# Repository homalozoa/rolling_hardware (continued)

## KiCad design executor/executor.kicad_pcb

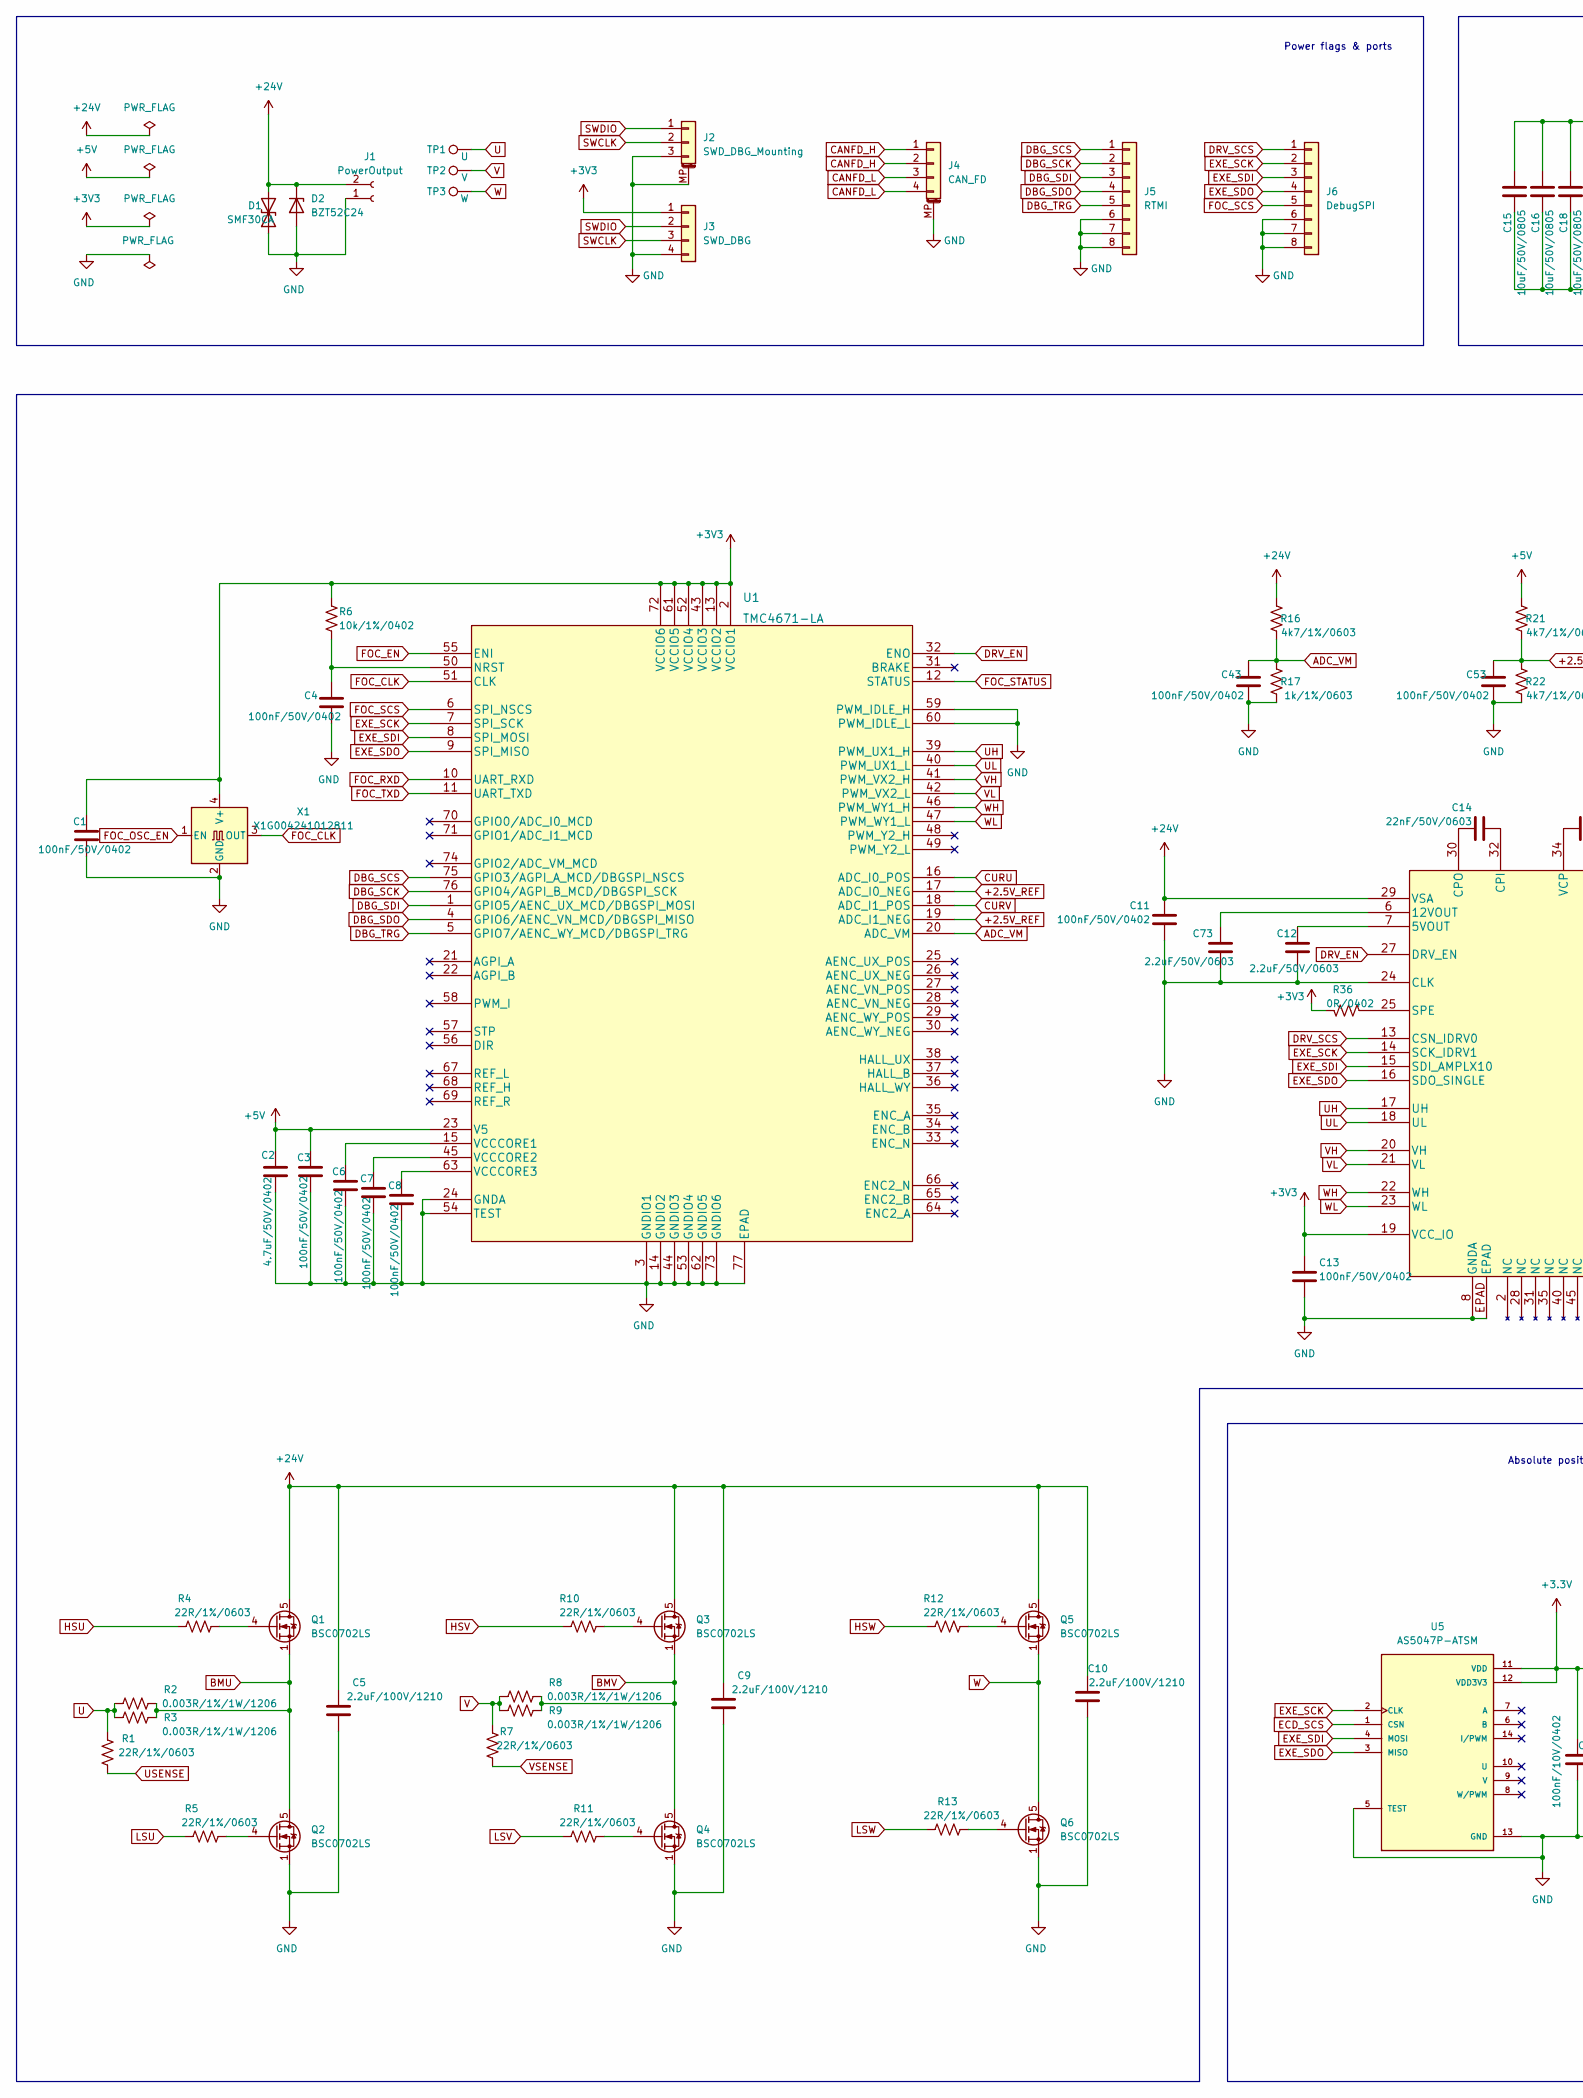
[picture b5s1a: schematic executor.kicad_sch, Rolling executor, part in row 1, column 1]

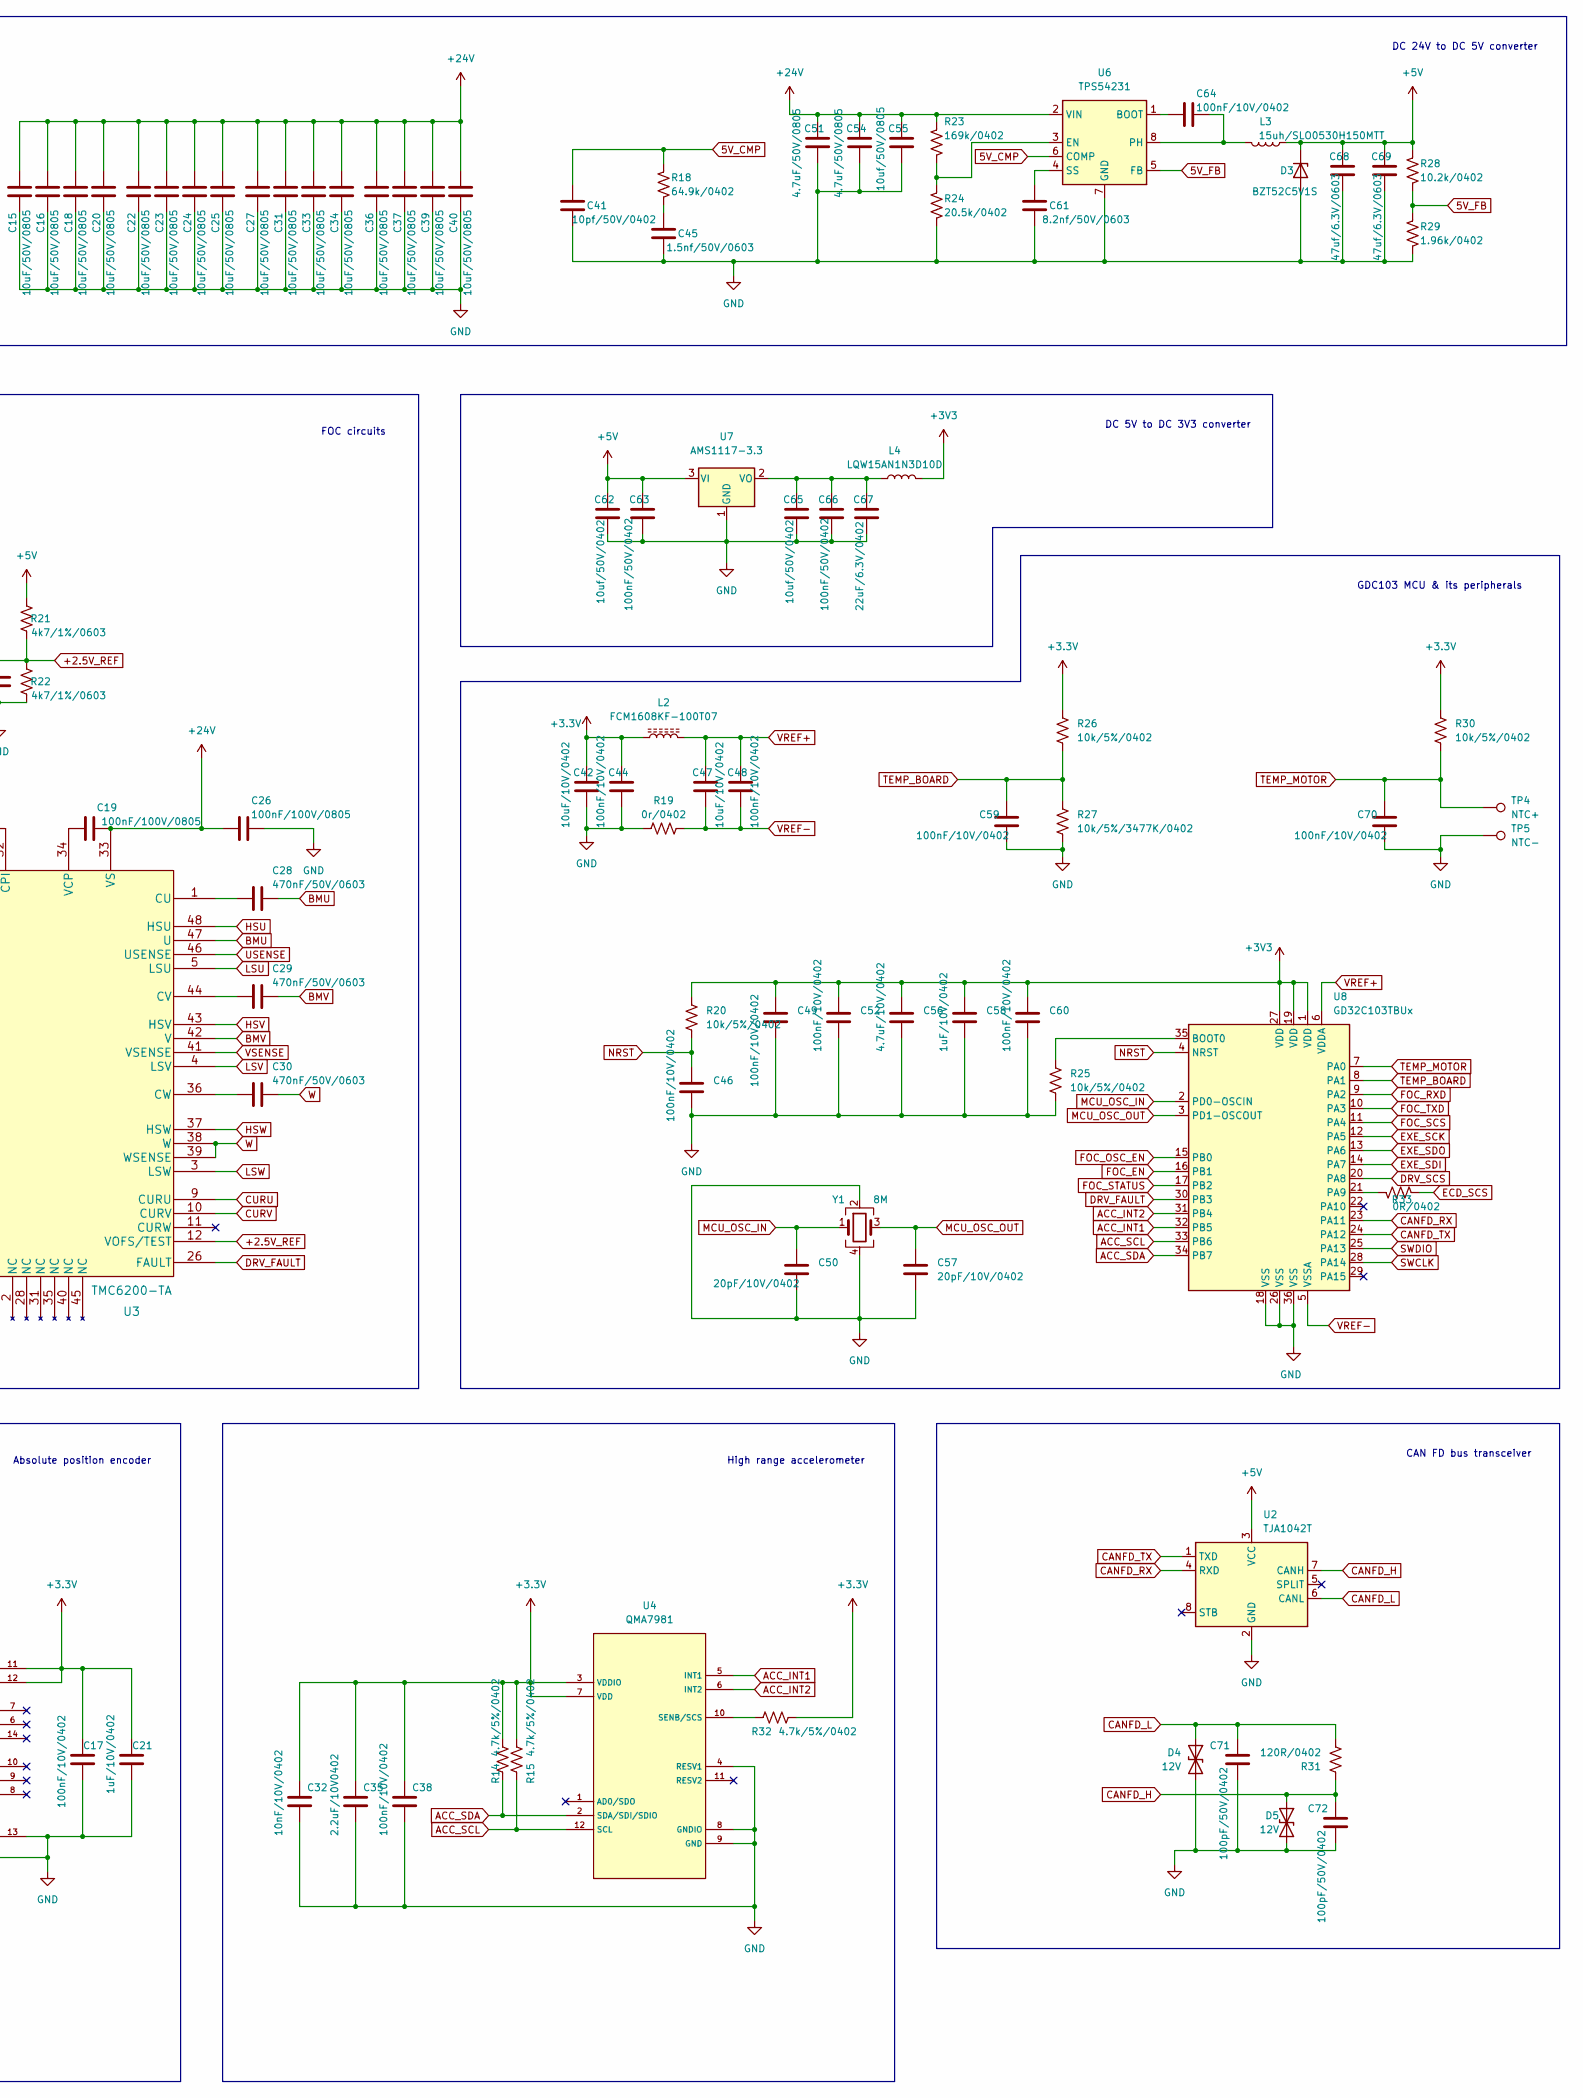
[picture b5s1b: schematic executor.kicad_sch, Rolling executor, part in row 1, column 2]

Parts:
C1, C3, C4, C6, C7, C8, C11, C13, C43, C53, C63, C66: 100nF/50V/0402; C_0402_1005Metric
C2: 4.7uF/50V/0402; C_0402_1005Metric
C5, C9, C10: 2.2uF/100V/1210; C_1210_3225Metric
C12, C73: 2.2uF/50V/0603; C_0603_1608Metric
C14: 22nF/50V/0603; C_0603_1608Metric
C15, C16, C18, C20, C22, C23, C24, C25, C27, C31, C33, C34, C36, C37, C39, C40: 10uF/50V/0805; C_0805_2012Metric
C17, C38, C44, C46, C48, C49, C52, C59, C60, C64, C70: 100nF/10V/0402; C_0402_1005Metric
C19, C26: 100nF/100V/0805; C_0805_2012Metric
C21, C58: 1uF/10V/0402; C_0402_1005Metric
C28, C29, C30: 470nF/50V/0603; C_0603_1608Metric
C32: 10nF/10V/0402; C_0402_1005Metric
C35: 2.2uF/10V0402; C_0402_1005Metric
C41: 10pf/50V/0402; C_0402_1005Metric
C42, C47: 10uF/10V/0402; C_0402_1005Metric
C45: 1.5nf/50V/0603; C_0603_1608Metric
C50, C57: 20pF/10V/0402; C_0402_1005Metric
C51, C54: 4.7uF/50V/0805; C_0805_2012Metric
C55: 10uf/50V/0805; C_0805_2012Metric
C56: 4.7uF/10V/0402; C_0402_1005Metric
C61: 8.2nf/50V/0603; C_0603_1608Metric
C62, C65: 10uf/50V/0402; C_0402_1005Metric
C67: 22uF/6.3V/0402; C_0402_1005Metric
C68, C69: 47uf/6.3V/0603; C_0603_1608Metric
C71, C72: 100pF/50V/0402; C_0402_1005Metric
D1: SMF30CA; D_SOD-123
D2: BZT52C24; D_SOD-123F
D3: BZT52C5V1S; D_SOD-123F
D4, D5: 12V; D_SOD-323
J1: PowerOutput; AMASS_XT30UPB-M_1x02_P5.0mm_Vertical
J2: SWD_DBG_Mounting; JST_GH_SM03B-GHS-TB_1x03-1MP_P1.25mm_Horizontal
J3: SWD_DBG; PinHeader_1x04_P1.27mm_Vertical
J4: CAN_FD; JST_GH_SM04B-GHS-TB_1x04-1MP_P1.25mm_Horizontal
J5: RTMI; FH34SRJ-6S-0.5SH50
J6: DebugSPI; FH34SRJ-6S-0.5SH50
L2: FCM1608KF-100T07; R_0603_1608Metric
L3: 15uh/SLO0530H150MTT; L_Sunlord_MWSA0518_5.4x5.2mm
L4: LQW15AN1N3D10D; L_0402_1005Metric
Q1, Q2, Q3, Q4, Q5, Q6: BSC0702LS; TDSON-8-1
R1, R4, R5, R7, R10, R11, R12, R13: 22R/1%/0603; R_0603_1608Metric
R2, R3, R8, R9: 0.003R/1%/1W/1206; R_1206_3216Metric
R6: 10k/1%/0402; R_0402_1005Metric
R14, R15, R32: 4.7k/5%/0402; R_0402_1005Metric
R16, R21, R22: 4k7/1%/0603; R_0603_1608Metric
R17: 1k/1%/0603; R_0603_1608Metric
R18: 64.9k/0402; R_0402_1005Metric
R19: 0r/0402; R_0402_1005Metric
R20, R25, R26, R30: 10k/5%/0402; R_0402_1005Metric
R23: 169k/0402; R_0402_1005Metric
R24: 20.5k/0402; R_0402_1005Metric
R27: 10k/5%/3477K/0402; R_0402_1005Metric
R28: 10.2k/0402; R_0402_1005Metric
R29: 1.96k/0402; R_0402_1005Metric
R31: 120R/0402; R_0402_1005Metric
R33, R36: 0R/0402; R_0402_1005Metric
TP1: U; TestPoint_Plated_Hole_D2.0mm
TP2: V; TestPoint_Plated_Hole_D2.0mm
TP3: W; TestPoint_Plated_Hole_D2.0mm
TP4: NTC+; TestPoint_THTPad_D1.0mm_Drill0.5mm
TP5: NTC-; TestPoint_THTPad_D1.0mm_Drill0.5mm
U1: TMC4671-LA; QFN76_10P5X6P5_TRI
U2: TJA1042T; SOIC-8_3.9x4.9mm_P1.27mm
U3: TMC6200-TA; eTQFP48_9x9_TRI
U4: QMA7981; LGA-12_2x2mm_P0.5mm
U5: AS5047P-ATSM; TSSOP-14_4.4x5mm_P0.65mm; PARTREV 1-01
U6: TPS54231; SOIC-8_3.9x4.9mm_P1.27mm
U7: AMS1117-3.3; SOT-223-3_TabPin2
U8: GD32C103TBUx; QFN-36-1EP_6x6mm_P0.5mm
X1: X1G004241012811; Crystal_SMD_3225-4Pin_3.2x2.5mm
Y1: 8M; Oscillator_SMD_ECS_2520MV-xxx-xx-4Pin_2.5x2.0mm

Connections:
5V_CMP: C41.1, R18.1, U6.6 (COMP)
5V_FB: R28.2, R29.1, U6.5 (FB)
+2.5V_REF: C53.2, R21.2, R22.1, U1.17 (ADC_I0_NEG), U1.19 (ADC_I1_NEG), U3.12 (VOFS/TEST)
+5V: C2.1, C3.2, C62.1, C63.1, C68.1, C69.1, D3.1 (K), L3.1, R21.1, R28.1, U1.23 (V5), U2.3 (VCC), U7.3 (VI)
+24V: C5.2, C9.2, C10.2, C11.2, C15.1, C16.1, C18.1, C19.1, C20.1, C22.1, C23.1, C24.1, C25.1, C26.1, C27.1, C31.1, C33.1, C34.1, C36.1, C37.1, C39.1, C40.1, C51.1, C54.1, C55.1, D1.2 (A2), D2.1 (K), J1.2, Q1.5 (D), Q3.5 (D), Q5.5 (D), R16.1, R23.1, U3.29 (VSA), U3.33 (VS), U6.2 (VIN)
ACC_INT1: U4.5 (INT1), U8.32 (PB5)
ACC_INT2: U4.6 (INT2), U8.31 (PB4)
ACC_SCL: R15.1, U4.12 (SCL), U8.33 (PB6)
ACC_SDA: R14.1, U4.2 (SDA/SDI/SDIO), U8.34 (PB7)
ADC_VM: C43.2, R16.2, R17.1, U1.20 (ADC_VM)
BMU: C28.2, Q1.1 (S), Q1.2 (S), Q1.3 (S), Q2.5 (D), R2.2, R3.2, U3.47 (U)
BMV: C29.2, Q3.1 (S), Q3.2 (S), Q3.3 (S), Q4.5 (D), R8.2, R9.2, U3.42 (V)
CANFD_H: C72.2, D5.1 (A1), J4.1, J4.2, R31.1, U2.7 (CANH)
CANFD_L: C71.2, D4.1 (A1), J4.3, J4.4, R31.2, U2.6 (CANL)
CANFD_RX: U2.4 (RXD), U8.23 (PA11)
CANFD_TX: U2.1 (TXD), U8.24 (PA12)
CURU: U1.16 (ADC_I0_POS), U3.9 (CURU)
CURV: U1.18 (ADC_I1_POS), U3.10 (CURV)
DBG_SCK: J5.2, U1.76 (GPIO4/AGPI_B_MCD/DBGSPI_SCK)
DBG_SCS: J5.1, U1.75 (GPIO3/AGPI_A_MCD/DBGSPI_NSCS)
DBG_SDI: J5.3, U1.1 (GPIO5/AENC_UX_MCD/DBGSPI_MOSI)
DBG_SDO: J5.4, U1.4 (GPIO6/AENC_VN_MCD/DBGSPI_MISO)
DBG_TRG: J5.5, U1.5 (GPIO7/AENC_WY_MCD/DBGSPI_TRG)
DRV_EN: U1.32 (ENO), U3.27 (DRV_EN)
DRV_FAULT: U3.26 (FAULT), U8.30 (PB3)
DRV_SCS: J6.1, U3.13 (CSN_IDRV0), U8.20 (PA8)
ECD_SCS: R33.1, U5.1 (CSN)
EXE_SCK: J6.2, U1.7 (SPI_SCK), U3.14 (SCK_IDRV1), U5.2 (CLK), U8.12 (PA5)
EXE_SDI: J6.3, U1.8 (SPI_MOSI), U3.15 (SDI_AMPLX10), U5.4 (MOSI), U8.14 (PA7)
EXE_SDO: J6.4, U1.9 (SPI_MISO), U3.16 (SDO_SINGLE), U5.3 (MISO), U8.13 (PA6)
FOC_CLK: U1.51 (CLK), X1.3 (OUT)
FOC_EN: U1.55 (ENI), U8.16 (PB1)
FOC_OSC_EN: U8.15 (PB0), X1.1 (EN)
FOC_RXD: U1.10 (UART_RXD), U8.9 (PA2)
FOC_SCS: J6.5, U1.6 (SPI_NSCS), U8.11 (PA4)
FOC_STATUS: U1.12 (STATUS), U8.17 (PB2)
FOC_TXD: U1.11 (UART_TXD), U8.10 (PA3)
GND: C1.1, C2.2, C3.1, C4.1, C5.1, C6.1, C7.1, C8.1, C9.1, C10.1, C11.1, C12.1, C13.1, C15.2, C16.2, C17.2, C18.2, C20.2, C21.2, C22.2, C23.2, C24.2, C25.2, C26.2, C27.2, C31.2, C32.2, C33.2, C34.2, C35.2, C36.2, C37.2, C38.2, C39.2, C40.2, C41.2, C42.1, C43.1, C44.1, C45.2, C46.2, C49.2, C50.1, C51.2, C52.2, C53.1, C54.2, C55.2, C56.2, C57.1, C58.2, C59.1, C60.2, C61.2, C62.2, C63.2, C65.2, C66.2, C67.2, C68.2, C69.2, C70.1, C71.1, C72.1, C73.1, D1.1 (A1), D2.2 (A), D3.2 (A), D4.2 (A2), D5.2 (A2), J1.1, J2.3, J2.MP (MountPin), J3.4, J4.MP (MountPin), J5.6, J5.7, J5.8, J6.6, J6.7, J6.8, Q2.1 (S), Q2.2 (S), Q2.3 (S), Q4.1 (S), Q4.2 (S), Q4.3 (S), Q6.1 (S), Q6.2 (S), Q6.3 (S), R17.2, R19.1, R22.2, R24.2, R25.2, R27.2, R29.2, TP5.1, U1.3 (GNDIO1), U1.14 (GNDIO2), U1.24 (GNDA), U1.44 (GNDIO3), U1.53 (GNDIO4), U1.54 (TEST), U1.59 (PWM_IDLE_H), U1.60 (PWM_IDLE_L), U1.62 (GNDIO5), U1.73 (GNDIO6), U1.77 (EPAD), U2.2 (GND), U3.8 (GNDA), U3.24 (CLK), U3.EPAD, U4.4 (RESV1), U4.8 (GNDIO), U4.9 (GND), U5.5 (TEST), U5.13 (GND), U6.7 (GND), U7.1 (GND), U8.18 (VSS), U8.26 (VSS), U8.36 (VSS), X1.2 (GND), Y1.2, Y1.4
HSU: R4.1, U3.48 (HSU)
HSV: R10.1, U3.43 (HSV)
HSW: R12.1, U3.37 (HSW)
LSU: R5.1, U3.5 (LSU)
LSV: R11.1, U3.4 (LSV)
LSW: R13.1, U3.3 (LSW)
MCU_OSC_IN: C50.2, U8.2 (PD0-OSCIN), Y1.1
MCU_OSC_OUT: C57.2, U8.3 (PD1-OSCOUT), Y1.3
NRST: C46.1, R20.2, U8.4 (NRST)
unnamed: C4.2, R6.2, U1.50 (NRST)
unnamed: C6.2, U1.15 (VCCCORE1)
unnamed: C7.2, U1.45 (VCCCORE2)
unnamed: C8.2, U1.63 (VCCCORE3)
unnamed: C12.2, U3.7 (5VOUT)
unnamed: C14.1, U3.32 (CPI)
unnamed: C14.2, U3.30 (CPO)
unnamed: C19.2, U3.34 (VCP)
unnamed: C28.1, U3.1 (CU)
unnamed: C29.1, U3.44 (CV)
unnamed: C30.1, U3.36 (CW)
unnamed: C45.1, R18.2
unnamed: C61.1, U6.4 (SS)
unnamed: C64.1, L3.2, U6.8 (PH)
unnamed: C64.2, U6.1 (BOOT)
unnamed: C65.1, C66.1, C67.1, L4.1, U7.2 (VO)
unnamed: C73.2, U3.6 (12VOUT)
unnamed: Q1.4 (G), R4.2
unnamed: Q2.4 (G), R5.2
unnamed: Q3.4 (G), R10.2
unnamed: Q4.4 (G), R11.2
unnamed: Q5.4 (G), R12.2
unnamed: Q6.4 (G), R13.2
unnamed: R23.2, R24.1, U6.3 (EN)
unnamed: R25.1, U8.35 (BOOT0)
unnamed: R32.1, U4.10 (SENB/SCS)
unnamed: R36.1, U3.25 (SPE)
unnamed: R33.2, U8.21 (PA9)
SWCLK: J2.2, J3.3, U8.28 (PA14)
SWDIO: J2.1, J3.2, U8.25 (PA13)
TEMP_BOARD: C59.2, R26.2, R27.1, U8.8 (PA1)
TEMP_MOTOR: C70.2, R30.2, TP4.1, U8.7 (PA0)
U: R1.2, R2.1, R3.1, TP1.1
UH: U1.39 (PWM_UX1_H), U3.17 (UH)
UL: U1.40 (PWM_UX1_L), U3.18 (UL)
USENSE: R1.1, U3.46 (USENSE)
V: R7.2, R8.1, R9.1, TP2.1
VH: U1.41 (PWM_VX2_H), U3.20 (VH)
VL: U1.42 (PWM_VX2_L), U3.21 (VL)
VREF+: C47.2, C48.2, L2.2, U8.6 (VDDA)
VREF-: C47.1, C48.1, R19.2, U8.5 (VSSA)
VSENSE: R7.1, U3.41 (VSENSE)
W: C30.2, Q5.1 (S), Q5.2 (S), Q5.3 (S), Q6.5 (D), TP3.1, U3.38 (W), U3.39 (WSENSE)
WH: U1.46 (PWM_WY1_H), U3.22 (WH)
WL: U1.47 (PWM_WY1_L), U3.23 (WL)

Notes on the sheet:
Absolute position encoder
High range accelerometer
FOC circuits
CAN FD bus transceiver
Power flags & ports
GDC103 MCU & its peripherals
DC 24V to DC 5V converter
DC 5V to DC 3V3 converter

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
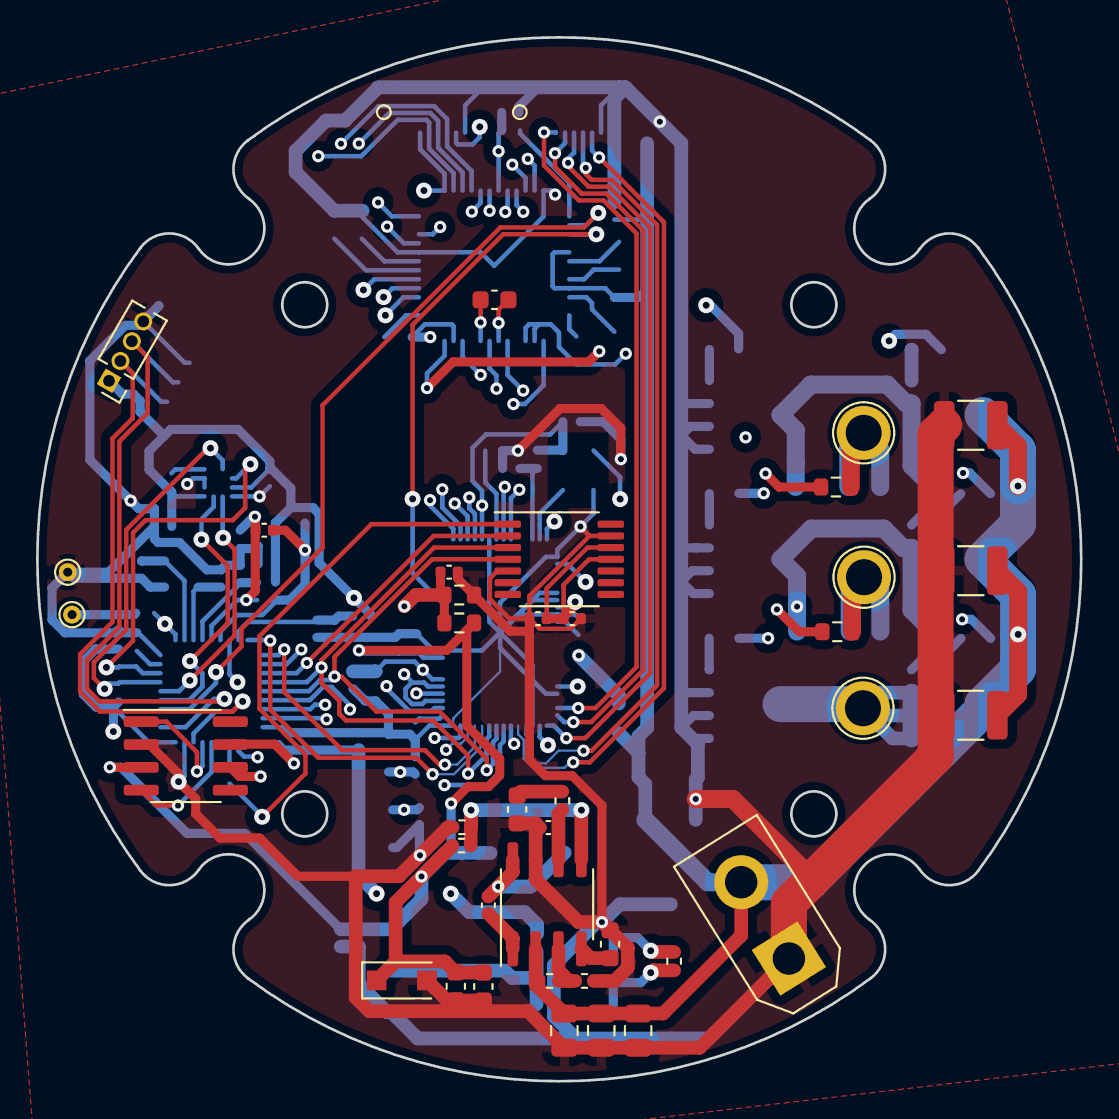
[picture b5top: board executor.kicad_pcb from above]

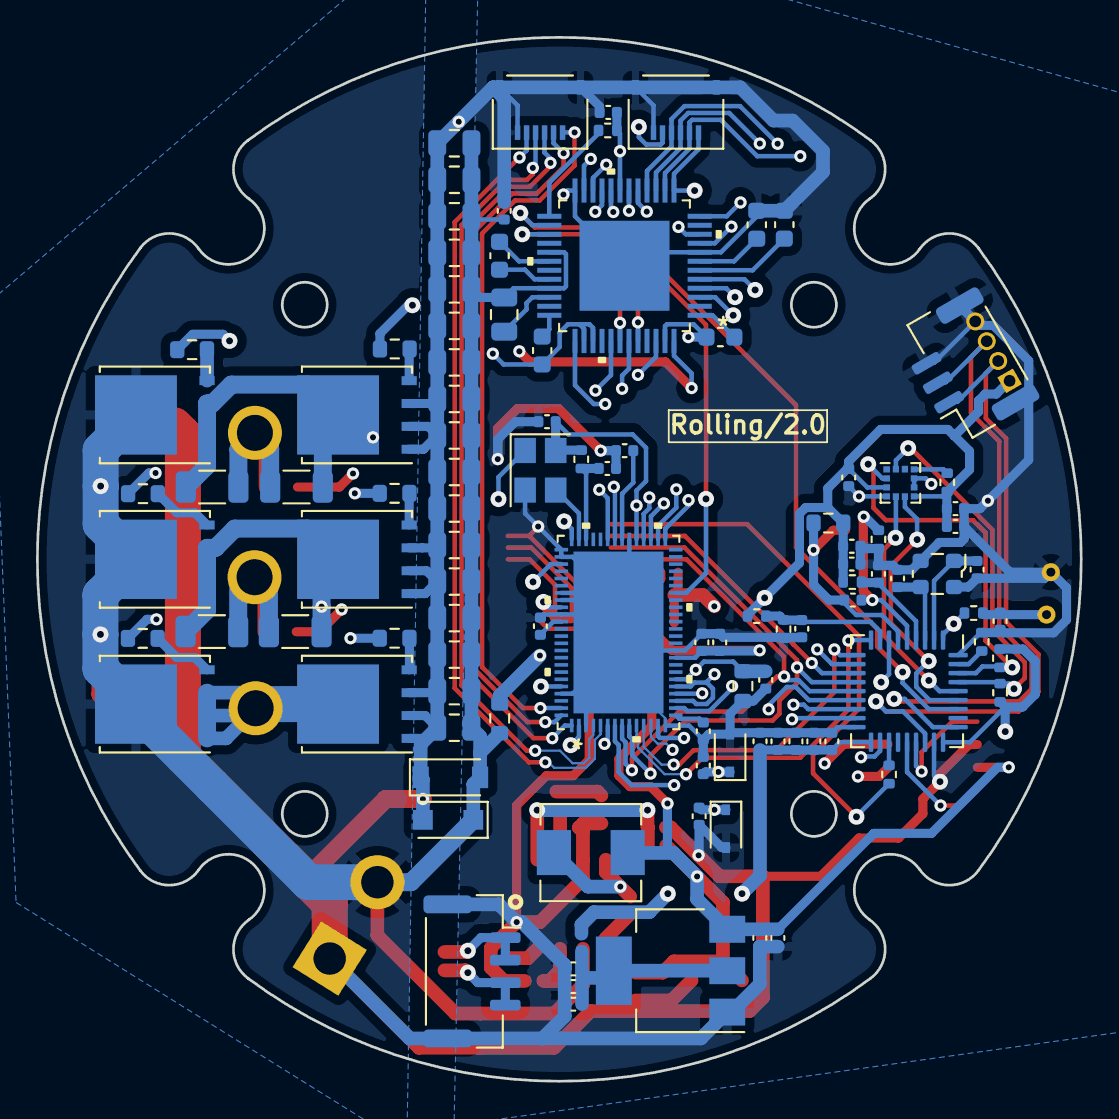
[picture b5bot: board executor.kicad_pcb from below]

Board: 4 copper layers, 58.0 x 58.0 mm, 142 parts (104 on the bottom side), 93 nets.

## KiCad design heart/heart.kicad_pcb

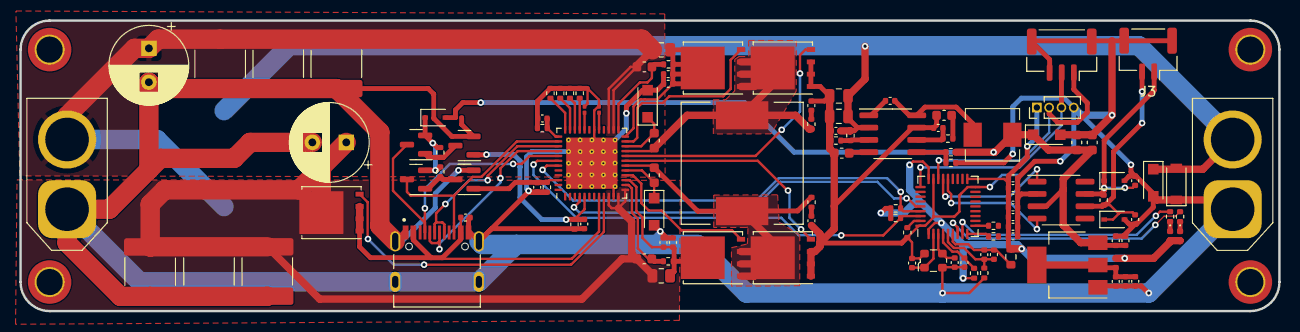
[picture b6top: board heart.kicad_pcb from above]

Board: 2 copper layers, 130.0 x 30.0 mm, 123 parts (1 on the bottom side), 67 nets.

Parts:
C1: 10pf 50V; C_0402_1005Metric
C2, C8, C14, C30: 10uf 50V; C_0402_1005Metric
C3: 1.5nf 50V; C_0603_1608Metric
C4, C11, C28, C36, C37, C39, C40, C42, C50: 100nF, 10%, 50V; C_0402_1005Metric
C5, C6: 100nF, 10%, 100V; C_0603_1608Metric
C7, C10: 4.7uF 50V; C_0805_2012Metric
C13: 22uF, 10%, 6.3V; C_0402_1005Metric
C15: 8.2nf 50V; C_0603_1608Metric
C16, C17: 100pF, 10%, 10V; C_0402_1005Metric
C18, C20, C22, C24, C29, C41, C46: 100nF, 10%, 10V; C_0402_1005Metric
C19, C21: 47uf 50V; C_0603_1608Metric
C23, C26: 20pF, 10%, 10V; C_0402_1005Metric
C25: 4.7uF, 10%, 10V; C_0402_1005Metric
C27: 1uF, 10%, 10V; C_0402_1005Metric
C31, C33: 1uf 50V; C_0603_1608Metric
C32, C34, C35: 2.2uf 50v; C_0201_0603Metric
C38, C44: 10uF, 10%, 10V; C_0402_1005Metric
C43, C49: 220uf; CP_Radial_D8.0mm_P3.50mm
C45, C47, C48, C51, C54, C55: 22uF,50V; C_2220_5650Metric
C52, C53: 1.5nF 50v; C_0402_1005Metric
D1: SMF30CA; D_SOD-123
D2: BZT52C24; D_SOD-123F
D3, D4: 12V; D_SOD-323
D5: BZT52C5V1S; D_SOD-123F
D6, D7: SMF30A; D_SOD-123F
D8: 1SS355; D_SOD-323
D9: 16-213/SDRC/S530-A3/TR8; D_0402_1005Metric
D10: 16-213/GHC-YR1S1/3T; D_0402_1005Metric
J1: BatteryPort; AMASS_XT60-M_1x02_P7.20mm_Vertical
J2: PowerOutput; AMASS_XT60-F_1x02_P7.20mm_Vertical
J3: CAN FD; JST_GH_SM02B-GHS-TB_1x02-1MP_P1.25mm_Horizontal
J4: SWD_DBG; PinHeader_1x04_P1.27mm_Vertical
J5: SWD_DBG_Mounting; JST_GH_SM03B-GHS-TB_1x03-1MP_P1.25mm_Horizontal
J8: TYPE-C-31-M-12; HRO_TYPE-C-31-M-12
L1: LQW15AN1N3D10D; L_0402_1005Metric
L2: 15uh, SLO0530H150MTT; L_Sunlord_MWSA0518_5.4x5.2mm
L3, L5: MWSA1206S-5R6MT; L_12x12mm_H6mm
L4: FCM1608KF-100T07; R_0603_1608Metric
Mount1, Mount1#2, Mount1#3, Mount1#4: MountingHole_2.7mm_M2.5_ISO7380_Pad_TopBottom
Q1: BSC0702LS; TDSON-8-1
Q2, Q6: 2301; SOT-23
Q3, Q7: 2N7002; SOT-23
Q4, Q5, Q8, Q9: NTMFS5C670NLT1G; TDSON-8-1
R1: 64.9k; R_0402_1005Metric
R2: 169k; R_0402_1005Metric
R3: 20.5; R_0402_1005Metric
R4: 120R; R_0402_1005Metric
R5, R8: 10k, 5%; R_0402_1005Metric
R6: 10.2k; R_0402_1005Metric
R7: 1.96k; R_0402_1005Metric
R9: 10k, 3380k; R_0402_1005Metric
R10, R11: 4.7k; R_0402_1005Metric
R12, R15: 27k; R_0402_1005Metric
R13: 6.2k; R_0402_1005Metric
R14, R22, R25: 10k; R_0402_1005Metric
R16, R17, R24: 0; R_0402_1005Metric
R18, R20: 10r; R_0402_1005Metric
R19, R21: 0.005r; R_0805_2012Metric
R23, R28: 1M; R_0402_1005Metric
R26, R27: 330r; R_0402_1005Metric
R29, R30: 2r; R_0402_1005Metric
U1: TJA1042T; SOIC-8_3.9x4.9mm_P1.27mm
U2: AMS1117-3.3; SOT-223-3_TabPin2
U3: TPS54231; SOIC-8_3.9x4.9mm_P1.27mm
U4: IP2368; QFN-48-1EP_7x7mm_P0.5mm_EP5.3x5.3mm_ThermalVias
U5: GD32C103TBUx; QFN-36-1EP_6x6mm_P0.5mm
Y1: 8M; Oscillator_SMD_ECS_2520MV-xxx-xx-4Pin_2.5x2.0mm

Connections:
5V_CMP: C1.1, R1.1, U3.6 (COMP)
5V_FB: R6.2, R7.1, U3.5 (FB)
+3V3: C22.1, C24.1, C25.1, C27.1, C29.1, C38.2, C41.2, D9.2 (A), D10.2 (A), J4.1, L1.2, L4.1, R5.1, R10.1, R11.1, U5.1 (VDD), U5.19 (VDD), U5.27 (VDD)
+5V: C2.1, C4.1, C19.1, C21.1, C32.1, D5.1 (K), D8.2 (A), L2.1, R6.1, U1.3 (VCC), U2.3 (VI)
+24V: C7.1, C10.1, C14.1, D1.2 (A2), D2.1 (K), J2.2, L3.2, R2.1, U3.2 (VIN)
+BATT: C31.2, C49.1, C51.1, C54.1, C55.1, J1.2, L3.1, R19.1, U4.26 (CSP2), U4.27 (BAT)
BAT_MODE: C50.1, Q7.1 (G), R28.2, U4.46 (BAT_MODE)
BST1: C5.1, D7.1 (A1), U4.17 (BST1)
BST1C: C5.2, L5.2, Q4.1 (S), Q4.2 (S), Q4.3 (S), Q8.5 (D), R29.1, U4.18 (LX1)
BST2: C6.1, D6.1 (A1), U4.22 (BST2)
BST2C: C6.2, L5.1, Q5.1 (S), Q5.2 (S), Q5.3 (S), Q9.5 (D), R30.1, U4.21 (LX2)
CANFD_H: C17.2, D4.1 (A1), J3.1, R4.1, U1.7 (CANH)
CANFD_L: C16.2, D3.1 (A1), J3.2, R4.2, U1.6 (CANL)
CANFD_RX: U1.4 (RXD), U5.23 (PA11)
CANFD_TX: U1.1 (TXD), U5.24 (PA12)
CH_INT: U4.4 (LED3/IIC_INT), U5.32 (PB5)
CH_SCL: R11.2, U4.43 (LED1/IIC_SCL), U5.33 (PB6)
CH_SDA: R10.2, U4.42 (LED2/IIC_SDA), U5.34 (PB7)
GND: C1.2, C2.2, C3.2, C4.2, C7.2, C8.2, C10.2, C11.2, C13.2, C14.2, C15.2, C16.1, C17.1, C19.2, C20.2, C21.2, C22.2, C23.1, C24.2, C25.2, C26.1, C27.2, C28.2, C29.2, C30.2, C32.2, C34.2, C35.2, C36.2, C37.2, C38.1, C39.2, C40.2, C41.1, C42.2, C43.2, C45.2, C47.2, C48.2, C49.2, C50.2, C51.2, C52.2, C53.2, C54.2, C55.2, D1.1 (A1), D2.2 (A), D3.2 (A2), D4.2 (A2), D5.2 (A), D6.2 (A2), D7.2 (A2), J1.1, J2.1, J3.MP (MountPin), J4.4, J5.3, J5.MP (MountPin), J8.A1B12 (GND), J8.B1A12 (GND), J8.S1 (SHIELD), J8.S2 (SHIELD), J8.S3 (SHIELD), J8.S4 (SHIELD), Q3.2 (S), Q7.2 (S), Q8.1 (S), Q8.2 (S), Q8.3 (S), Q9.1 (S), Q9.2 (S), Q9.3 (S), R3.2, R7.2, R8.2, R9.2, R12.2, R13.2, R14.2, R15.2, R23.1, R24.1, R28.1, U1.2 (GND), U2.1 (GND), U3.7 (GND), U4.11 (AGND), U4.30 (AGND), U4.49 (GND), U5.18 (VSS), U5.26 (VSS), U5.36 (VSS), Y1.2, Y1.4
HG1: Q4.4 (G), U4.16 (HG1)
HG2: Q5.4 (G), U4.23 (HG2)
HLED: C42.1, Q3.1 (G), R23.2, U4.5 (HLED)
LED_GREEN: R27.1, U5.8 (PA1)
LED_RED: R26.1, U5.7 (PA0)
LG1: Q8.4 (G), U4.19 (LG1)
LG2: Q9.4 (G), U4.20 (LG2)
MCU_OSC_IN: C23.2, U5.2 (PD0-OSCIN), Y1.1
MCU_OSC_OUT: C26.2, U5.3 (PD1-OSCOUT), Y1.3
NRST: C20.1, R5.2, U5.4 (NRST)
NTC: C28.1, R9.1, U4.37 (NTC)
unnamed: C3.1, R1.2
unnamed: C8.1, C11.1, C13.1, L1.1, U2.2 (VO)
unnamed: C15.1, U3.4 (SS)
unnamed: C18.1, L2.2, U3.8 (PH)
unnamed: C18.2, U3.1 (BOOT)
unnamed: C31.1, R18.2, U4.25 (CSN2)
unnamed: C33.2, R20.2, U4.14 (CSN1)
unnamed: C36.1, C39.1, Q4.5 (D), R20.1, R21.2, U4.15 (PCIN)
unnamed: C37.1, C40.1, Q5.5 (D), R18.1, R19.2, U4.24 (PCON)
unnamed: C52.1, R29.2
unnamed: C53.1, R30.2
unnamed: D8.1 (K), Q2.2 (S), Q6.2 (S), R22.2, R25.2
unnamed: D9.1 (K), R26.2
unnamed: D10.1 (K), R27.2
unnamed: Q1.4 (G), U4.9 (VBUSG)
unnamed: Q2.1 (G), Q3.3 (D), R22.1
unnamed: Q6.1 (G), Q7.3 (D), R25.1
unnamed: R2.2, R3.1, U3.3 (EN)
unnamed: R8.1, U5.35 (BOOT0)
unnamed: R12.1, U4.33 (BAT_NUM)
unnamed: R13.1, U4.34 (FCAP)
unnamed: R14.1, U4.35 (VSET)
unnamed: R15.1, U4.36 (ISET)
unnamed: R16.1, U5.9 (PA2)
unnamed: R17.1, U5.10 (PA3)
SWCLK: J4.3, J5.2, U5.28 (PA14)
SWDIO: J4.2, J5.1, U5.25 (PA13)
USB_CC1: J8.A5 (CC1), Q2.3 (D), U4.41 (CC1)
USB_CC2: J8.B5 (CC2), Q6.3 (D), U4.38 (CC2)
USB_DN: J8.A7 (DN1), J8.B7 (DN2), U4.40 (DMC)
USB_DP: J8.A6 (DP1), J8.B6 (DP2), U4.39 (DPC)
USB_VBUS_D: C33.1, C43.1, C45.1, C47.1, C48.1, Q1.5 (D), R21.1, U4.10 (VBUSI), U4.12 (VIO), U4.13 (CSP1)
USB_VBUS_S: C30.1, J8.A4B9 (VBUS), J8.B4A9 (VBUS), Q1.1 (S), Q1.2 (S), Q1.3 (S), U4.8 (VBUS)
VCC5V: C34.1, U4.29 (VCC5V)
VCCIO: C35.1, U4.32 (VCCIO)
VREF+: C44.2, C46.2, L4.2, U5.6 (VDDA)
VREF-: C44.1, C46.1, R24.2, U5.5 (VSSA)

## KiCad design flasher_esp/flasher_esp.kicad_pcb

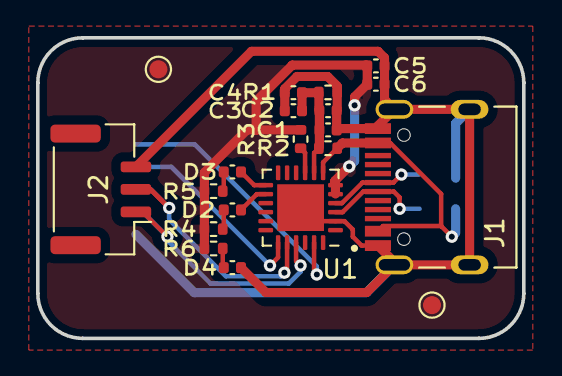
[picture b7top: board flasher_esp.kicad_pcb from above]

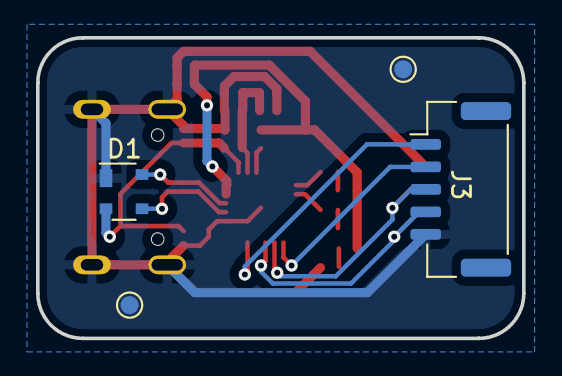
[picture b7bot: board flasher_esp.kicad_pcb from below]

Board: 2 copper layers, 27.0 x 16.7 mm, 20 parts (2 on the bottom side), 16 nets.

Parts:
C1, C6: 0.1uf; C_0402_1005Metric
C2, C5: 4.7uf; C_0402_1005Metric
C3: 1uf; C_0402_1005Metric
C4: 100uf; C_0402_1005Metric
D1: SP0503BAHT; SOT-143
D2: MHT136UBCT; C_0402_1005Metric
D3: NCD0402G1; C_0402_1005Metric
D4: NCD0402W1; C_0402_1005Metric
J1: TYPE-C-31-M-12; HRO_TYPE-C-31-M-12
J2: UART_NPWR; JST_GH_BM03B-GHS-TBT_1x03-1MP_P1.25mm_Vertical
J3: UART_FLASH_ESP; JST_GH_BM05B-GHS-TBT_1x05-1MP_P1.25mm_Vertical
R1: 47.5k; R_0402_1005Metric
R2: 22.1k; R_0402_1005Metric
R3: 1k; R_0402_1005Metric
R4, R5, R6: 200R; R_0402_1005Metric
U1: CP2102N-A02-GQFN24; QFN-24-1EP_4x4mm_P0.5mm_EP2.6x2.6mm

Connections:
+3V3: C5.1, C6.1, R3.2, R4.1, R5.1, R6.1, U1.5 (VIO), U1.6 (VDD)
+5V: D1.2 (K), J1.A4B9 (VBUS), J1.B4A9 (VBUS), R2.1, U1.7 (VREGIN)
D+: D1.3 (K), J1.A6 (DP1), U1.3 (D+)
D-: D1.4 (K), J1.A7 (DN1), U1.4 (D-)
DTR: J3.1, U1.23 (DTR)
GND: C1.2, C2.2, C3.2, C4.2, C5.2, C6.2, D1.1 (A), D4.1 (K), J1.A1B12 (GND), J1.B1A12 (GND), J1.S1 (SHIELD), J1.S2 (SHIELD), J1.S3 (SHIELD), J1.S4 (SHIELD), J2.3, J3.5, R1.2, U1.2 (GND_1), U1.25 (GND_2)
unnamed: C1.1, C2.1, C3.1, C4.1, R1.1, R2.2, U1.8 (VBUS)
unnamed: D2.2 (A), R4.2
unnamed: D3.2 (A), R5.2
unnamed: D4.2 (A), R6.2
unnamed: R3.1, U1.9 (RSTB)
RTS: J3.2, U1.19 (RTS)
RXD: J2.2, J3.3, U1.20 (RXD)
RXT: D3.1 (K), U1.13 (GPIO.1_/_RXT)
TXD: J2.1, J3.4, U1.21 (TXD)
TXT: D2.1 (K), U1.14 (GPIO.0_/_TXT)

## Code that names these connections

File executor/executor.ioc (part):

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Mcu.Name=STM32F103R(C-D-E)Tx
Mcu.Package=LQFP64
Mcu.UserName=STM32F103RETx
PA0-WKUP.GPIOParameters=GPIO_Label
PA0-WKUP.GPIO_Label=VSEN_BUS
PA0-WKUP.Signal=ADCx_IN0
PA1.GPIOParameters=GPIO_Label
PA1.GPIO_Label=TEMP_BOARD
PA1.Signal=ADCx_IN1
PA10.GPIOParameters=GPIO_Label
PA10.GPIO_Label=PWM_C
PA10.Signal=S_TIM1_CH3
PA11.GPIOParameters=GPIO_Label
PA11.GPIO_Label=DRV_EN
PA11.Signal=GPIO_Output
PA15.Mode=NSS_Signal_Hard_Output
PA15.Signal=SPI3_NSS
PA4.GPIOParameters=GPIO_Label
PA4.GPIO_Label=DRV_SCS
PA4.Mode=NSS_Signal_Hard_Output
PA4.Signal=SPI1_NSS
PA5.GPIOParameters=GPIO_Label
PA5.GPIO_Label=DRV_SCK
PA5.Mode=Full_Duplex_Master
PA5.Signal=SPI1_SCK
PA6.GPIOParameters=GPIO_Label
PA6.GPIO_Label=DRV_SDO
PA6.Mode=Full_Duplex_Master
PA6.Signal=SPI1_MISO
PA7.GPIOParameters=GPIO_Label
PA7.GPIO_Label=DRV_SDI
PA7.Mode=Full_Duplex_Master
PA7.Signal=SPI1_MOSI
PA8.GPIOParameters=GPIO_Label
PA8.GPIO_Label=PWM_A
PA8.Signal=S_TIM1_CH1
PA9.GPIOParameters=GPIO_Label
PA9.GPIO_Label=PWM_B
PA9.Signal=S_TIM1_CH2
PB10.GPIOParameters=GPIO_Label
PB10.GPIO_Label=ACC_SCL
PB10.Mode=I2C
PB10.Signal=I2C2_SCL
PB11.GPIOParameters=GPIO_Label
PB11.GPIO_Label=ACC_SDA
PB11.Mode=I2C
PB11.Signal=I2C2_SDA
PB12.Mode=NSS_Signal_Hard_Output
PB12.Signal=SPI2_NSS
PB13.Mode=Full_Duplex_Master
PB13.Signal=SPI2_SCK
PB14.Mode=Full_Duplex_Master
PB14.Signal=SPI2_MISO
PB15.Mode=Full_Duplex_Master
PB15.Signal=SPI2_MOSI
PB3.Mode=Full_Duplex_Master
PB3.Signal=SPI3_SCK
PB4.Mode=Full_Duplex_Master
PB4.Signal=SPI3_MISO
PB5.Mode=Full_Duplex_Master
PB5.Signal=SPI3_MOSI
PC0.GPIOParameters=GPIO_Label
PC0.GPIO_Label=ISENSE_C
PC0.Signal=ADCx_IN10
PC1.GPIOParameters=GPIO_Label
PC1.GPIO_Label=ISENSE_B
PC1.Signal=ADCx_IN11
PC2.GPIOParameters=GPIO_Label
PC2.GPIO_Label=ISENSE_A
PC2.Signal=ADCx_IN12
PC3.GPIOParameters=GPIO_Label
PC3.GPIO_Label=TEMP_MOTOR
PC3.Signal=ADCx_IN13
PC6.GPIOParameters=GPIO_Label
PC6.GPIO_Label=TCAN_RST
PC6.Signal=GPIO_Output
PC7.GPIOParameters=GPIO_Label
PC7.GPIO_Label=TCAN_INT
PC7.Signal=GPXTI7
PC8.GPIOParameters=GPIO_Label
PC8.GPIO_Label=TCAN_WKRQ
PC8.Signal=GPIO_Output
PD0-OSC_IN.Mode=HSE-External-Oscillator
PD0-OSC_IN.Signal=RCC_OSC_IN
PD1-OSC_OUT.Mode=HSE-External-Oscillator
PD1-OSC_OUT.Signal=RCC_OSC_OUT
RCC.SYSCLKFreq_VALUE=72000000
RCC.SYSCLKSource=RCC_SYSCLKSOURCE_PLLCLK
board=custom

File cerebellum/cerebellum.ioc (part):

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Mcu.Name=STM32F401V(B-C)Tx
Mcu.Package=LQFP100
Mcu.UserName=STM32F401VBTx
PA13.Mode=Serial_Wire
PA13.Signal=SYS_JTMS-SWDIO
PA14.Mode=Serial_Wire
PA14.Signal=SYS_JTCK-SWCLK
PA15.GPIOParameters=GPIO_Label
PA15.GPIO_Label=ACC_SCS
PA15.Mode=NSS_Signal_Hard_Output
PA15.Signal=SPI3_NSS
PA4.GPIOParameters=GPIO_Label
PA4.GPIO_Label=TCAN_SCS
PA4.Mode=NSS_Signal_Hard_Output
PA4.Signal=SPI1_NSS
PA5.GPIOParameters=GPIO_Label
PA5.GPIO_Label=TCAN_SCK
PA5.Mode=Full_Duplex_Master
PA5.Signal=SPI1_SCK
PA6.GPIOParameters=GPIO_Label
PA6.GPIO_Label=TCAN_SDO
PA6.Mode=Full_Duplex_Master
PA6.Signal=SPI1_MISO
PA7.GPIOParameters=GPIO_Label
PA7.GPIO_Label=TCAN_SDI
PA7.Mode=Full_Duplex_Master
PA7.Signal=SPI1_MOSI
PA8.GPIOParameters=GPIO_Label
PA8.GPIO_Label=TCAN_RST
PA8.Signal=GPIO_Output
PA9.GPIOParameters=GPIO_Label
PA9.GPIO_Label=TCAN_INT
PA9.Signal=GPXTI9
PB12.GPIOParameters=GPIO_Label
PB12.GPIO_Label=ICP_SCS
PB12.Mode=NSS_Signal_Hard_Output
PB12.Signal=SPI2_NSS
PB13.GPIOParameters=GPIO_Label
PB13.GPIO_Label=ICP_SCK
PB13.Mode=Full_Duplex_Master
PB13.Signal=SPI2_SCK
PB14.GPIOParameters=GPIO_Label
PB14.GPIO_Label=ICP_INT
PB14.Signal=GPXTI14
PB3.GPIOParameters=GPIO_Label
PB3.GPIO_Label=BMI_HEAT
PB3.Signal=S_TIM2_CH2
PC10.GPIOParameters=GPIO_Label
PC10.GPIO_Label=BMI__SCK
PC10.Mode=Full_Duplex_Master
PC10.Signal=SPI3_SCK
PC11.GPIOParameters=GPIO_Label
PC11.GPIO_Label=BMI_SDO
PC11.Mode=Full_Duplex_Master
PC11.Signal=SPI3_MISO
PC12.GPIOParameters=GPIO_Label
PC12.GPIO_Label=BMI_SDI
PC12.Mode=Full_Duplex_Master
PC12.Signal=SPI3_MOSI
PC2.GPIOParameters=GPIO_Label
PC2.GPIO_Label=ICP_SDO
PC2.Mode=Full_Duplex_Master
PC2.Signal=SPI2_MISO
PC3.GPIOParameters=GPIO_Label
PC3.GPIO_Label=ICP_SDI
PC3.Mode=Full_Duplex_Master
PC3.Signal=SPI2_MOSI
PC9.GPIOParameters=GPIO_Label
PC9.GPIO_Label=TCAN_WKRQ
PC9.Signal=GPIO_Output
PD0.GPIOParameters=GPIO_Label
PD0.GPIO_Label=GYRO_SCS
PD0.Signal=GPIO_Output
PD1.GPIOParameters=GPIO_Label
PD1.GPIO_Label=BMI_INT1
PD1.Signal=GPXTI1
PD2.GPIOParameters=GPIO_Label
PD2.GPIO_Label=BMI_INT2
PD2.Signal=GPXTI2
PD3.GPIOParameters=GPIO_Label
PD3.GPIO_Label=BMI_INT3
PD3.Signal=GPXTI3
PD4.GPIOParameters=GPIO_Label
PD4.GPIO_Label=BMI_INT4
PD4.Signal=GPXTI4
PE2.Mode=Full_Duplex_Master
PE2.Signal=SPI4_SCK
PE4.Mode=NSS_Signal_Hard_Output
PE4.Signal=SPI4_NSS
PE5.Mode=Full_Duplex_Master
PE5.Signal=SPI4_MISO
PE6.Mode=Full_Duplex_Master
PE6.Signal=SPI4_MOSI
PH0\ -\ OSC_IN.Mode=HSE-External-Oscillator
PH0\ -\ OSC_IN.Signal=RCC_OSC_IN
PH1\ -\ OSC_OUT.Mode=HSE-External-Oscillator
PH1\ -\ OSC_OUT.Signal=RCC_OSC_OUT
RCC.HSE_VALUE=8000000
RCC.SYSCLKFreq_VALUE=84000000
RCC.SYSCLKSource=RCC_SYSCLKSOURCE_PLLCLK
board=custom
